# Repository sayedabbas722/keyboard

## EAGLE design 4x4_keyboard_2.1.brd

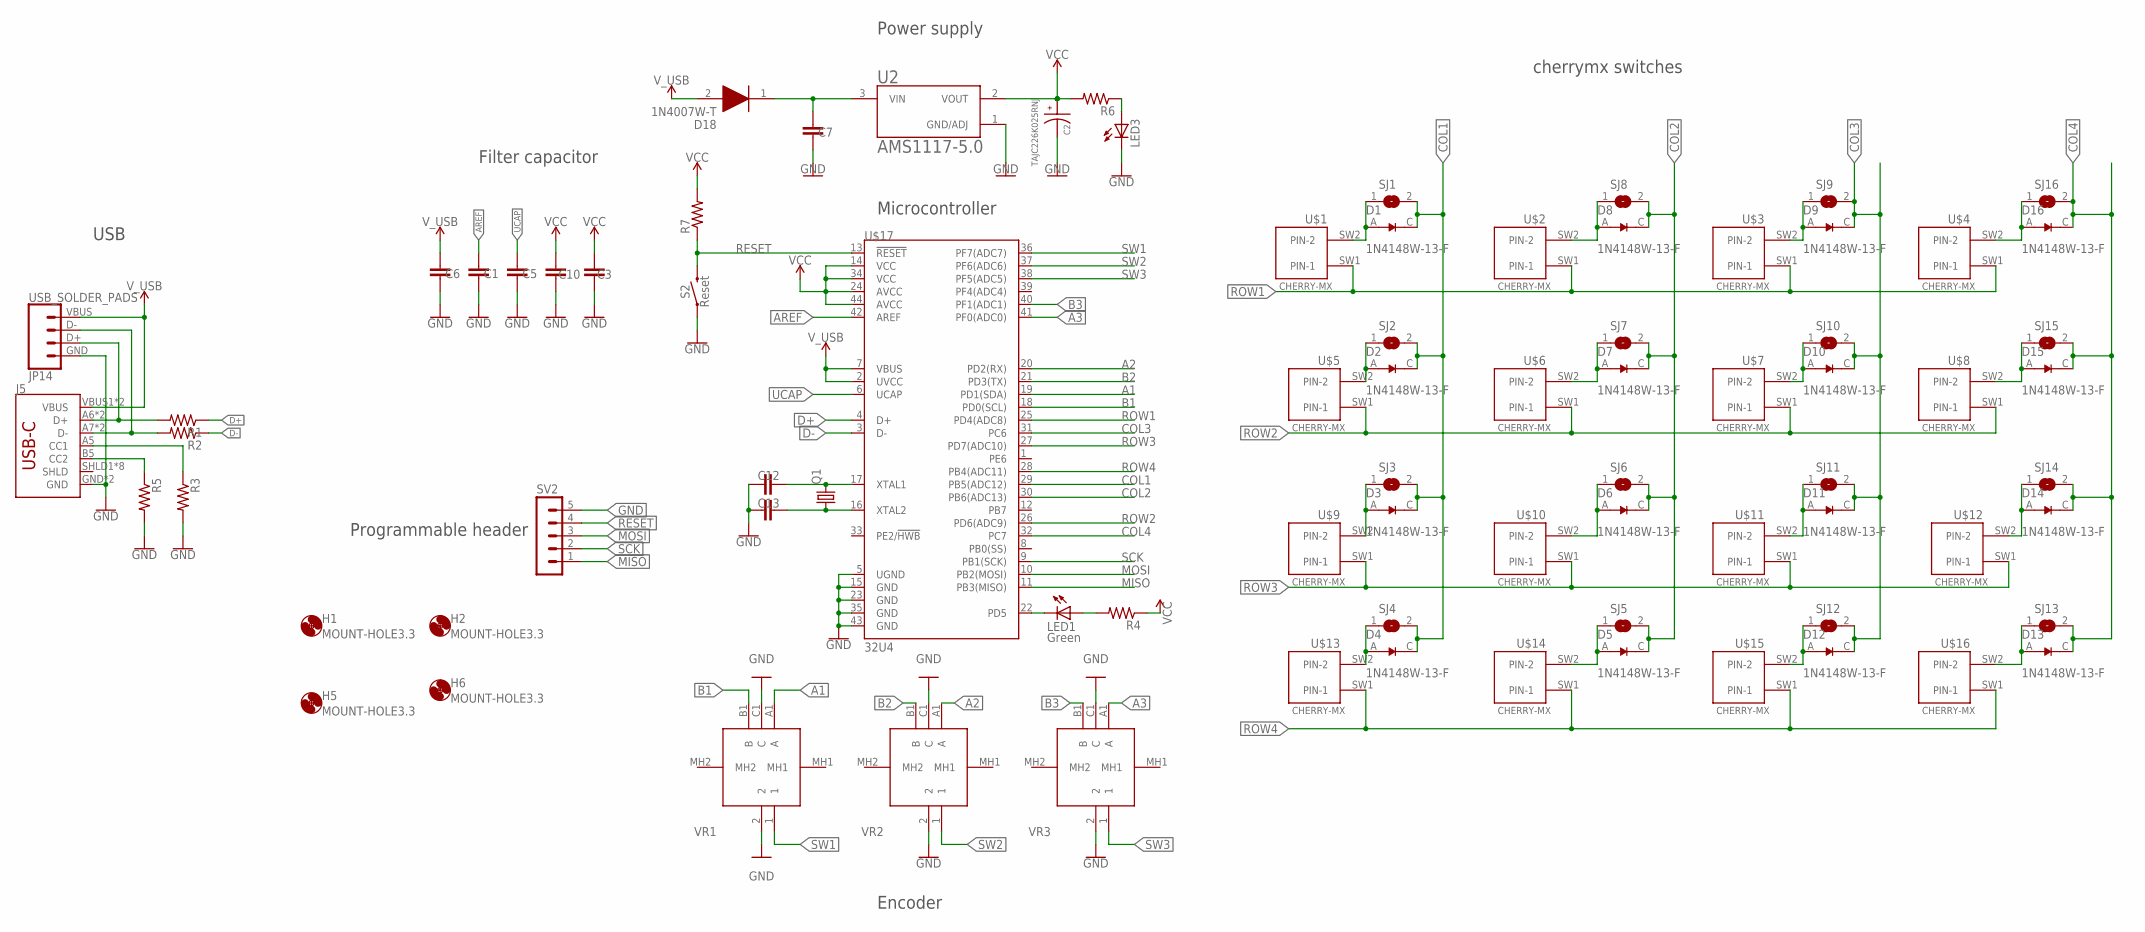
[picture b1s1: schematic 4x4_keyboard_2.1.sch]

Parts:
C1, C3: 0.1uF; C0603
C2: TAJC226K025RNJ; CAPPM6032X280N
C5, C6, C10: 1.0uF; C0603
C7: 10uF; C0603
C12, C13: 22pF; C0603
D1, D2, D3, D4, D5, D6, D7, D8, D9, D10, D11, D12, D13, D14, D15, D16: 1N4148W-13-F; SOD3715X135N
D18: 1N4007W-T; SODFL3818X130N
H1, H2, H5, H6: MOUNT-HOLE3.3; 3,3
J5: USB_C5; USB-C-16P-5
JP14: USB_SOLDER_PADS; USB-SOLDER-PADS
LED1: Green; SML0805
LED3: LEDSML0805; SML0805
Q1: CRYSTALHC49UP; HC49UP
R1, R2, R3, R5: 5.1k; R0603
R4, R6, R7: 1K; R0603
S2: Reset; TACTILE_SWITCH_SMD_4.6X2.8MM
SJ1, SJ2, SJ3, SJ4, SJ5, SJ6, SJ7, SJ8, SJ9, SJ10, SJ11, SJ12, SJ13, SJ14, SJ15, SJ16: SJ
SV2: MA05-1
U2: AMS1117-5.0; SOT229P700X180-4N
U$1, U$2, U$3, U$4, U$5, U$6, U$7, U$8, U$9, U$10, U$11, U$12, U$13, U$14, U$15, U$16: CHERRY-MX
U$17: 32U4; TQFP44
VR1, VR2, VR3: PEC11R-4220F-S0024; PEC11R4220FS0024

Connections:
A1: U$17.19 (PD1(SDA)), VR1.A1 (A)
A2: U$17.20 (PD2(RX)), VR2.A1 (A)
A3: U$17.41 (PF0(ADC0)), VR3.A1 (A)
AREF: C1.2, U$17.42 (AREF)
B1: U$17.18 (PD0(SCL)), VR1.B1 (B)
B2: U$17.21 (PD3(TX)), VR2.B1 (B)
B3: U$17.40 (PF1(ADC1)), VR3.B1 (B)
COL1: D1.C (K), D2.C (K), D3.C (K), D4.C (K), SJ1.2, SJ2.2, SJ3.2, SJ4.2, U$17.29 (PB5(ADC12))
COL2: D5.C (K), D6.C (K), D7.C (K), D8.C (K), SJ5.2, SJ6.2, SJ7.2, SJ8.2, U$17.30 (PB6(ADC13))
COL3: D9.C (K), D10.C (K), D11.C (K), D12.C (K), SJ9.2, SJ10.2, SJ11.2, SJ12.2, U$17.31 (PC6)
COL4: D13.C (K), D14.C (K), D15.C (K), D16.C (K), SJ13.2, SJ14.2, SJ15.2, SJ16.2, U$17.32 (PC7)
D+: R1.1, U$17.4 (D+)
D-: R2.1, U$17.3 (D-)
D-_HV: J5.A7 (D-), J5.B7 (D-), JP14.D- (2), R2.2
DP_HV: J5.A6 (D+), J5.B6 (D+), JP14.D+ (3), R1.2
GND: C1.1, C2.2, C3.1, C5.1, C6.1, C7.1, C10.1, C12.2, C13.2, J5.GND, J5.GND2 (GND), JP14.GND (4), LED3.C, R3.2, R5.2, S2.1, S2.2 (1), SV2.5, U2.1 (GND/ADJ), U$17.5 (UGND), U$17.15 (GND), U$17.23 (GND), U$17.35 (GND), U$17.43 (GND), VR1.2, VR1.C1 (C), VR2.2, VR2.C1 (C), VR3.2, VR3.C1 (C)
MISO: SV2.1, U$17.11 (PB3(MISO))
MOSI: SV2.3, U$17.10 (PB2(MOSI))
unnamed: LED1.C, U$17.22 (PD5)
unnamed: D3.A, SJ3.1, U$9.SW2 (PIN-2)
unnamed: C7.2, D18.1 (K), U2.3 (VIN)
unnamed: LED1.A, R4.2
unnamed: D4.A, SJ4.1, U$13.SW2 (PIN-2)
unnamed: J5.A5 (CC1), R3.1
unnamed: D16.A, SJ16.1, U$4.SW2 (PIN-2)
unnamed: D11.A, SJ11.1, U$11.SW2 (PIN-2)
unnamed: D15.A, SJ15.1, U$8.SW2 (PIN-2)
unnamed: LED3.A, R6.1
unnamed: D14.A, SJ14.1, U$12.SW2 (PIN-2)
unnamed: J5.B5 (CC2), R5.1
unnamed: D13.A, SJ13.1, U$16.SW2 (PIN-2)
unnamed: D12.A, SJ12.1, U$15.SW2 (PIN-2)
unnamed: D10.A, SJ10.1, U$7.SW2 (PIN-2)
unnamed: D9.A, SJ9.1, U$3.SW2 (PIN-2)
unnamed: D5.A, SJ5.1, U$14.SW2 (PIN-2)
unnamed: D2.A, SJ2.1, U$5.SW2 (PIN-2)
unnamed: D6.A, SJ6.1, U$10.SW2 (PIN-2)
unnamed: D7.A, SJ7.1, U$6.SW2 (PIN-2)
unnamed: C13.1, Q1.1, U$17.16 (XTAL2)
unnamed: D8.A, SJ8.1, U$2.SW2 (PIN-2)
unnamed: D1.A, SJ1.1, U$1.SW2 (PIN-2)
unnamed: C12.1, Q1.2, U$17.17 (XTAL1)
RESET: R7.1, S2.3 (2), S2.4 (2), SV2.4, U$17.13 (!RESET)
ROW1: U$1.SW1 (PIN-1), U$2.SW1 (PIN-1), U$3.SW1 (PIN-1), U$4.SW1 (PIN-1), U$17.25 (PD4(ADC8))
ROW2: U$5.SW1 (PIN-1), U$6.SW1 (PIN-1), U$7.SW1 (PIN-1), U$8.SW1 (PIN-1), U$17.26 (PD6(ADC9))
ROW3: U$9.SW1 (PIN-1), U$10.SW1 (PIN-1), U$11.SW1 (PIN-1), U$12.SW1 (PIN-1), U$17.27 (PD7(ADC10))
ROW4: U$13.SW1 (PIN-1), U$14.SW1 (PIN-1), U$15.SW1 (PIN-1), U$16.SW1 (PIN-1), U$17.28 (PB4(ADC11))
SCK: SV2.2, U$17.9 (PB1(SCK))
SW1: U$17.36 (PF7(ADC7)), VR1.1
SW2: U$17.37 (PF6(ADC6)), VR2.1
SW3: U$17.38 (PF5(ADC5)), VR3.1
UCAP: C5.2, U$17.6 (UCAP)
VCC: C2.1, C3.2, C10.2, R4.1, R6.2, R7.2, U2.2 (VOUT), U$17.14 (VCC), U$17.24 (AVCC), U$17.34 (VCC), U$17.44 (AVCC)
V_USB: C6.2, D18.2 (A), J5.VBUS1 (VBUS), J5.VBUS2 (VBUS), JP14.VBUS (1), U$17.2 (UVCC), U$17.7 (VBUS)

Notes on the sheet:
Power supply
Filter capacitor
USB
Programmable header
Encoder
cherrymx switches
Microcontroller

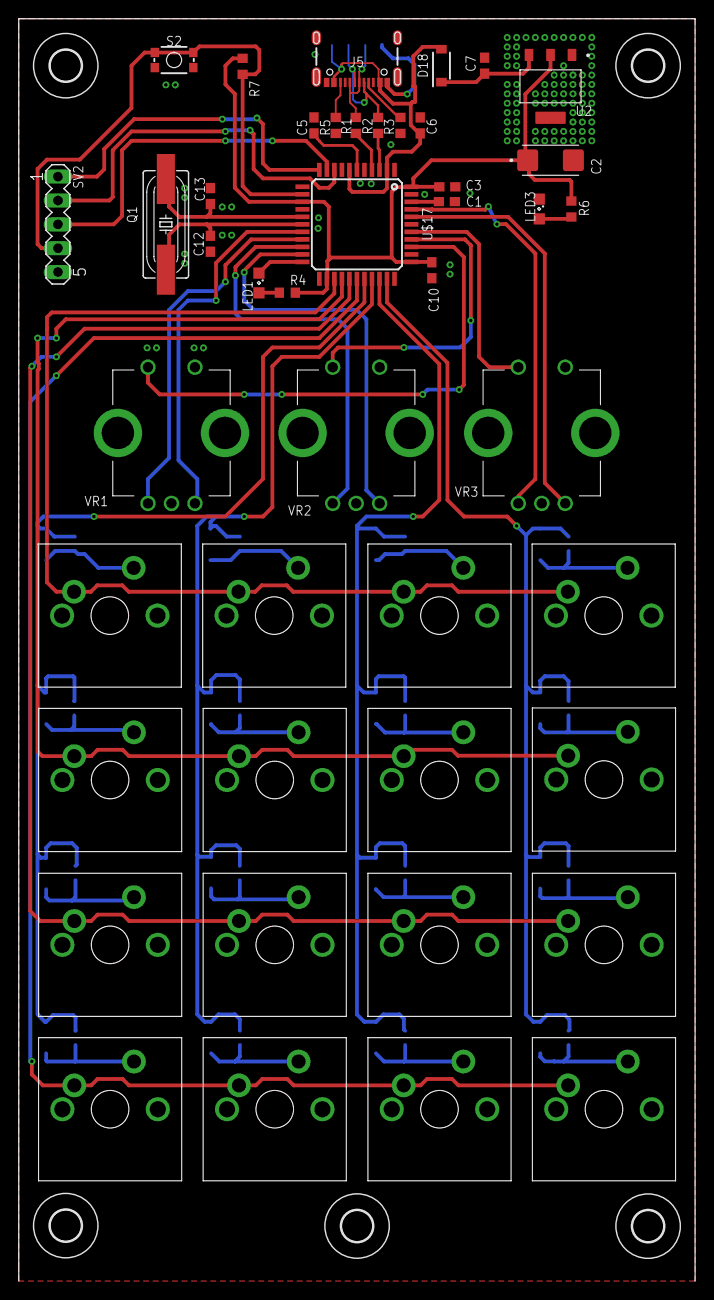
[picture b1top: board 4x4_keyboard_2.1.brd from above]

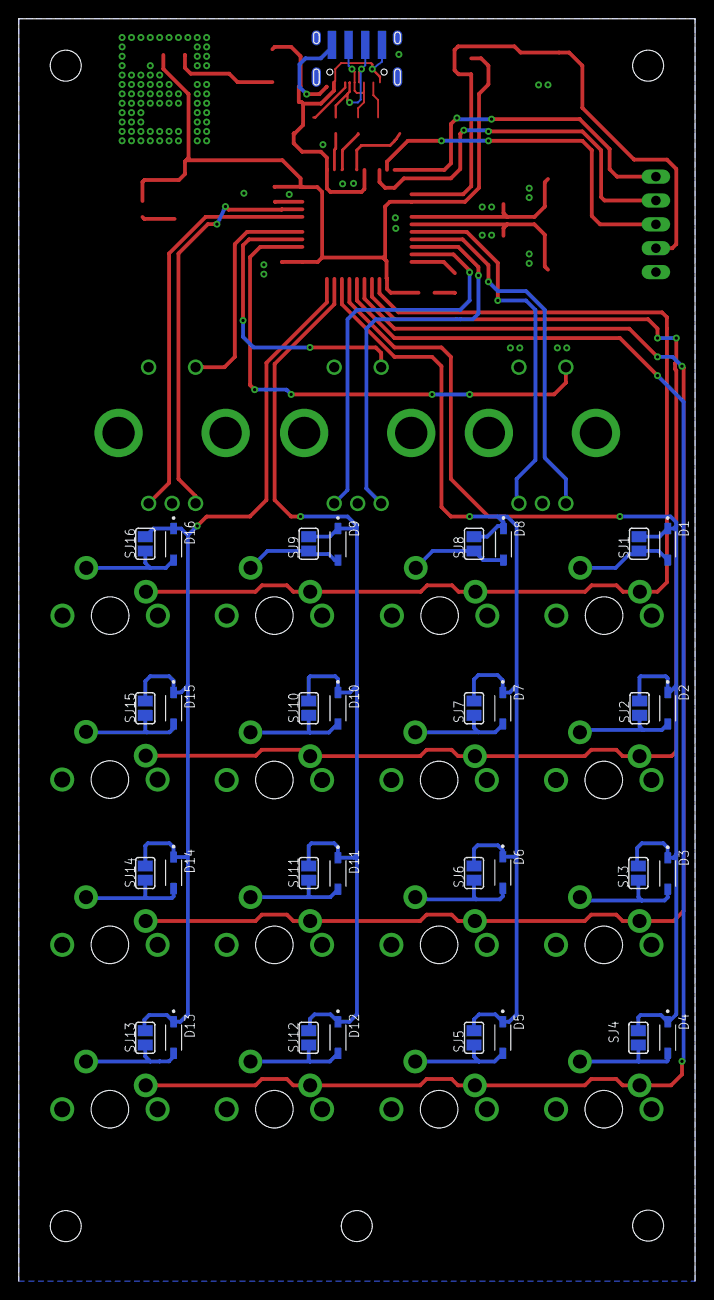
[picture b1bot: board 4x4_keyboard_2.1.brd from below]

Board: 2 copper layers, 72.0 x 134.4 mm, 82 parts (33 on the bottom side), 54 nets.

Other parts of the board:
H4: MOUNT-HOLE3.3; 3,3

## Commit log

2022-04-10 Keyboard sch and brd file
2022-04-10 place component to location
2022-04-10 switch routing
2022-04-10 change the position of component
2022-04-10 Switches routing complete
2022-04-10 Routing compelte of uc
2022-04-10 Correct routing signal
2022-04-10 complete the routing of encoder and changer it analogpins
2022-04-10 Complete the routing and error free
2022-04-10 Change forward diode package
2022-04-10 final output
2022-04-10 Added the usb c and usb A package
2022-04-10 change resistor package
2022-04-10 USB C is connect and final output without error
2022-04-10 change location of cherry switches
2022-04-12 routing cherry mx switch and correct the position of diode and rotary encoder
2022-04-13 make position uniform
2022-04-13 Routing is almost complete with error
2022-04-14 Routing complete
2022-04-16 added log
2022-04-16 make component placement perfect
2022-04-16 remove the logo and prog led for testing
2022-06-27 design files

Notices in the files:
parts and their libraries:
SparkFun-Connectors: Licensing: Creative Commons ShareAlike 4.0 International - https://creativecommons.org/licenses/by-sa/4.0
